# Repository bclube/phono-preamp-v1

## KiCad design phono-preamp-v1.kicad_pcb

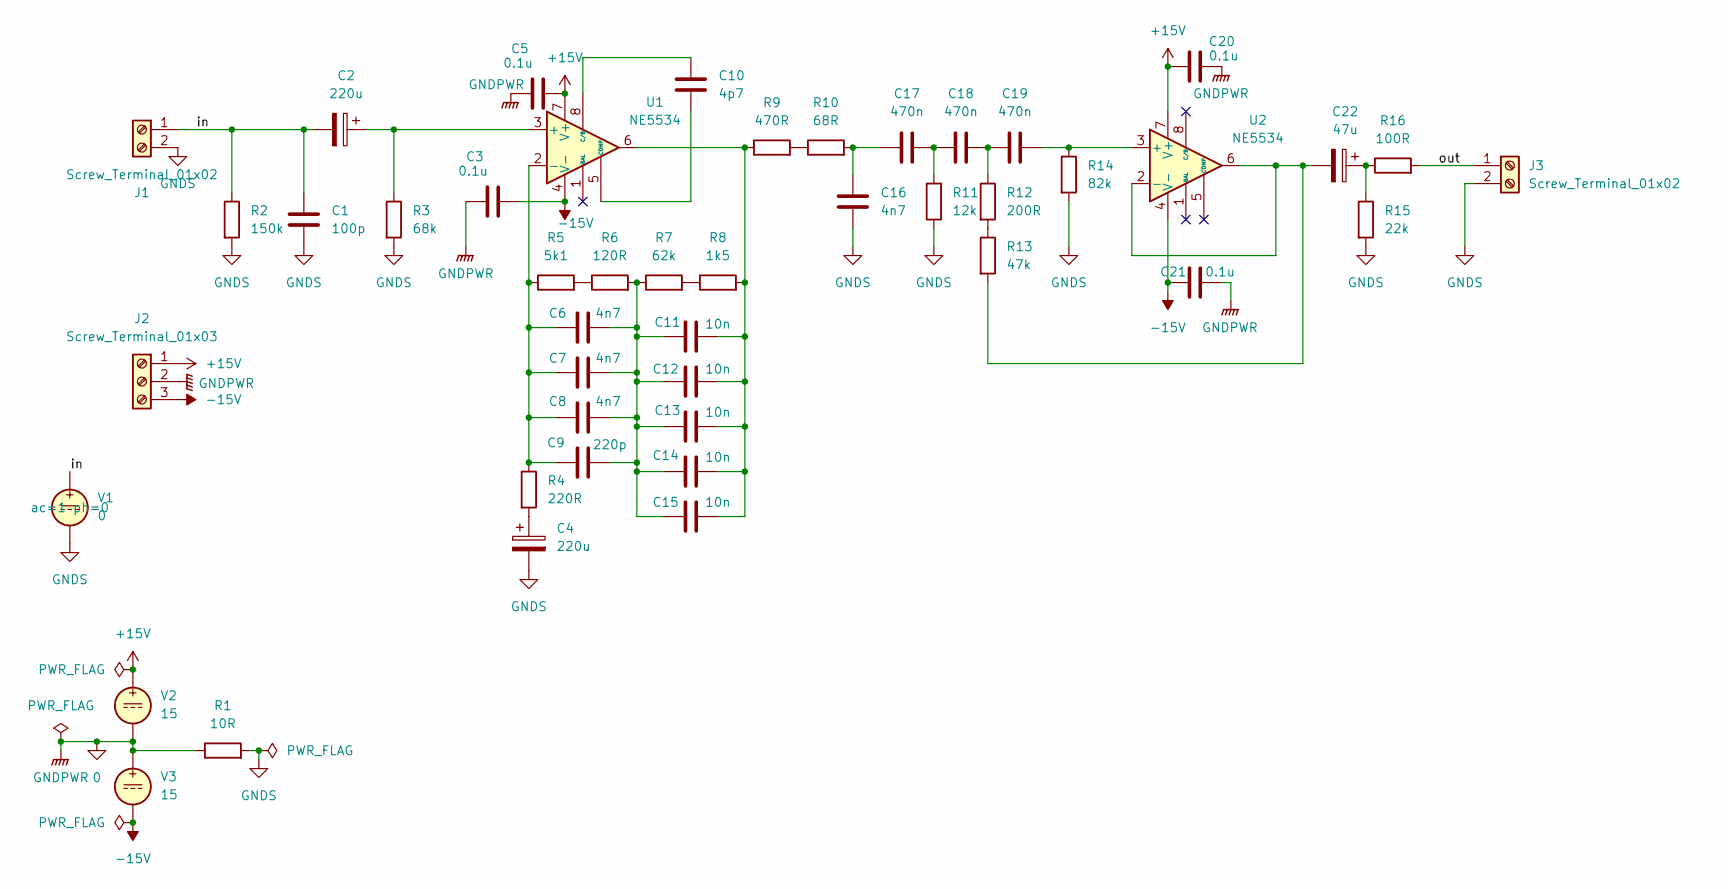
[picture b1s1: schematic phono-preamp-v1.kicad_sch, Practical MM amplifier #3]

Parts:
C1: 100p; C_0805_2012Metric_Pad1.18x1.45mm_HandSolder
C2, C4: 220u; C_Radial_D6.3mm_H11.0mm_P2.50mm
C3, C5, C20, C21: 0.1u; C_0805_2012Metric_Pad1.18x1.45mm_HandSolder
C6, C7, C8, C16: 4n7; C_0805_2012Metric_Pad1.18x1.45mm_HandSolder
C9: 220p; C_0805_2012Metric_Pad1.18x1.45mm_HandSolder
C10: 4p7; C_0805_2012Metric_Pad1.18x1.45mm_HandSolder
C11, C12, C13, C14, C15: 10n; C_0805_2012Metric_Pad1.18x1.45mm_HandSolder
C17, C18, C19: 470n; C_0805_2012Metric_Pad1.18x1.45mm_HandSolder
C22: 47u; C_Radial_D4.0mm_H7.0mm_P1.50mm
J1, J3: Screw_Terminal_01x02; TerminalBlock_bornier-2_P5.08mm
J2: Screw_Terminal_01x03; TerminalBlock_bornier-3_P5.08mm
R1: 10R; R_0805_2012Metric_Pad1.20x1.40mm_HandSolder
R2: 150k; R_0805_2012Metric_Pad1.20x1.40mm_HandSolder
R3: 68k; R_0805_2012Metric_Pad1.20x1.40mm_HandSolder
R4: 220R; R_0805_2012Metric_Pad1.20x1.40mm_HandSolder
R5: 5k1; R_0805_2012Metric_Pad1.20x1.40mm_HandSolder
R6: 120R; R_0805_2012Metric_Pad1.20x1.40mm_HandSolder
R7: 62k; R_0805_2012Metric_Pad1.20x1.40mm_HandSolder
R8: 1k5; R_0805_2012Metric_Pad1.20x1.40mm_HandSolder
R9: 470R; R_0805_2012Metric_Pad1.20x1.40mm_HandSolder
R10: 68R; R_0805_2012Metric_Pad1.20x1.40mm_HandSolder
R11: 12k; R_0805_2012Metric_Pad1.20x1.40mm_HandSolder
R12: 200R; R_0805_2012Metric_Pad1.20x1.40mm_HandSolder
R13: 47k; R_0805_2012Metric_Pad1.20x1.40mm_HandSolder
R14: 82k; R_0805_2012Metric_Pad1.20x1.40mm_HandSolder
R15: 22k; R_0805_2012Metric_Pad1.20x1.40mm_HandSolder
R16: 100R; R_0805_2012Metric_Pad1.20x1.40mm_HandSolder
U1, U2: NE5534; SOIC-8_3.9x4.9mm_P1.27mm
V1: 0
V2, V3: 15

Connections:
0: C3.1, C5.1, C20.2, C21.2, J2.2, R1.1, V2.2, V3.1
+15V: C5.2, C20.1, J2.1, U1.7 (V+), U2.7 (V+), V2.1
-15V: C3.2, C21.1, J2.3, U1.4 (V-), U2.4 (V-), V3.2
/in: C1.1, C2.2, J1.1, R2.1, V1.1
/out: J3.1, R16.2
GNDS: C1.2, C4.2, C16.1, J1.2, J3.2, R1.2, R2.2, R3.2, R11.1, R14.2, R15.2, V1.2
unnamed: C4.1, R4.2
unnamed: C6.2, C7.2, C8.2, C9.2, C11.1, C12.1, C13.1, C14.1, C15.1, R6.2, R7.1
unnamed: C11.2, C12.2, C13.2, C14.2, C15.2, R8.2, R9.1, U1.6
unnamed: C16.2, C17.1, R10.2
unnamed: C17.2, C18.1, R11.2
unnamed: C18.2, C19.1, R12.1
unnamed: C22.1, R15.1, R16.1
unnamed: R5.2, R6.1
unnamed: R7.2, R8.1
unnamed: R9.2, R10.1
unnamed: R12.2, R13.1
unnamed: C2.1, R3.1, U1.3 (+)
unnamed: C6.1, C7.1, C8.1, C9.1, R4.1, R5.1, U1.2 (-)
unnamed: C10.2, U1.5 (COMP)
unnamed: C10.1, U1.8 (C/B)
unnamed: C19.2, R14.1, U2.3 (+)
unnamed: C22.2, R13.2, U2.2 (-), U2.6

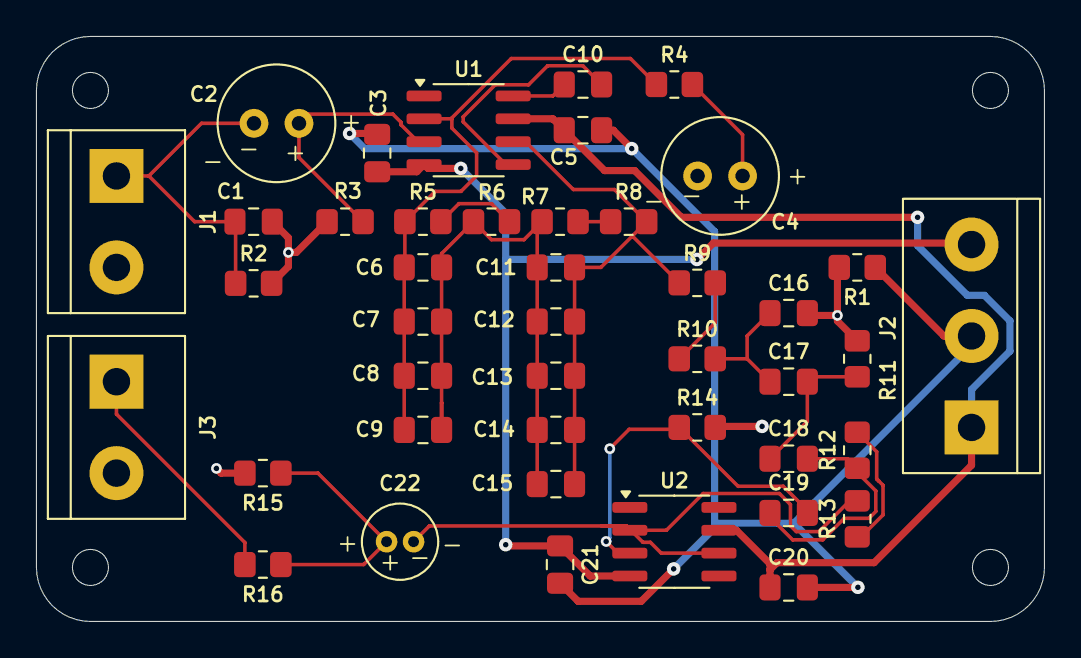
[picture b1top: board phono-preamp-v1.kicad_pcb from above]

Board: 2 copper layers, 56.0 x 32.5 mm, 43 parts (0 on the bottom side), 23 nets.

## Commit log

2025-12-29 Add initial KiCad project files for phono preamp design
2025-12-29 Complete setup of schematic page
2025-12-29 Add symbols to schematic
2025-12-29 Arrange symbols; add footprints
2025-12-29 Add component values
2025-12-29 Reannotate symbols; clean up schematic; run simulations
2025-12-29 Add power input; reannotate
2025-12-29 Initial PCB Layout; all signal ground connected
2025-12-29 Run critical power traces
2025-12-30 Complete routing; shrink board size
